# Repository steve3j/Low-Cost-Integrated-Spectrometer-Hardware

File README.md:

# Low-Cost-Integrated-Spectrometer-Hardware
Hardware for LCI Spectrometer - ECE 445 Senior Design project

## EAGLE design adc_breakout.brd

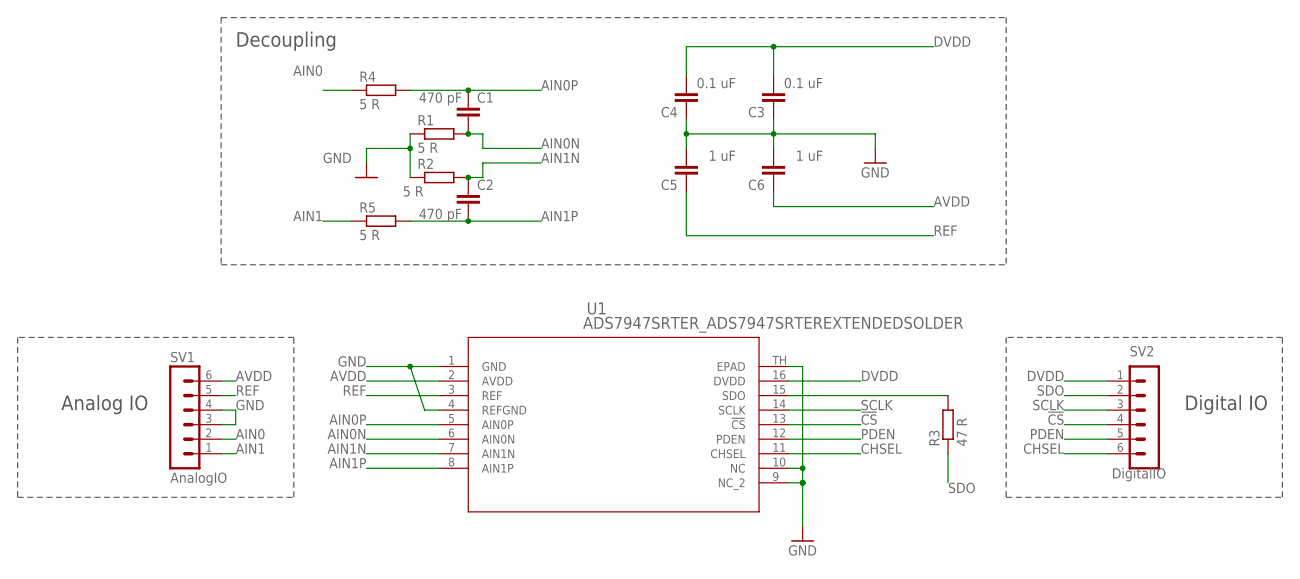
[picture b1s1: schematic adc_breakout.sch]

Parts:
C1, C2: 470 pF; C0603
C3, C4: 0.1 uF; C0603
C5, C6: 1 uF; C0603
R1, R2, R4, R5: 5 R; R0603
R3: 47 R; R0603
SV1: AnalogIO; MA06-1
SV2: DigitalIO; MA06-1
U1: ADS7947SRTER_ADS7947SRTEREXTENDEDSOLDER; QFN16-EXTENDEDPADS

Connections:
!CS: SV2.4, U1.13 (!CS)
AIN0: R4.1, SV1.2
AIN0N: C1.2, R1.2, U1.6 (AIN0N)
AIN0P: C1.1, R4.2, U1.5 (AIN0P)
AIN1: R5.1, SV1.1
AIN1N: C2.1, R2.2, U1.7 (AIN1N)
AIN1P: C2.2, R5.2, U1.8 (AIN1P)
AVDD: C6.1, SV1.6, U1.2 (AVDD)
CHSEL: SV2.6, U1.11 (CHSEL)
DVDD: C3.2, C4.2, SV2.1, U1.16 (DVDD)
GND: C3.1, C4.1, C5.2, C6.2, R1.1, R2.1, SV1.3, SV1.4, U1.1 (GND), U1.4 (REFGND), U1.9 (NC_2), U1.10 (NC), U1.TH (EPAD)
unnamed: R3.2, U1.15 (SDO)
PDEN: SV2.5, U1.12 (PDEN)
REF: C5.1, SV1.5, U1.3 (REF)
SCLK: SV2.3, U1.14 (SCLK)
SDO: R3.1, SV2.2

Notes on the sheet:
Decoupling
Analog IO
Digital IO

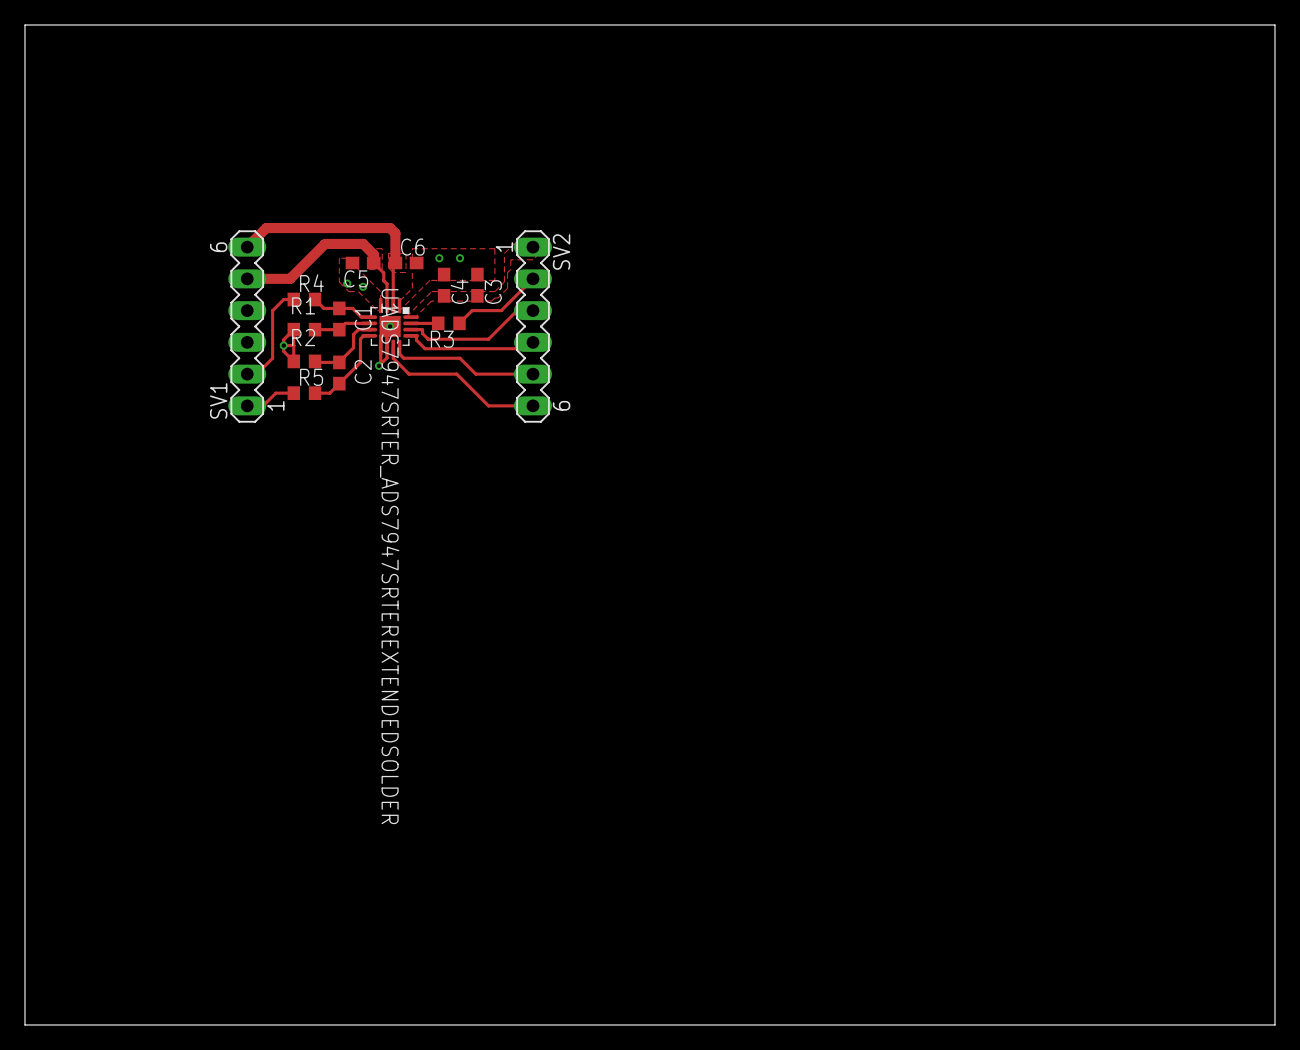
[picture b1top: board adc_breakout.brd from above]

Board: 2 copper layers, 100.0 x 80.0 mm, 14 parts (0 on the bottom side), 16 nets.

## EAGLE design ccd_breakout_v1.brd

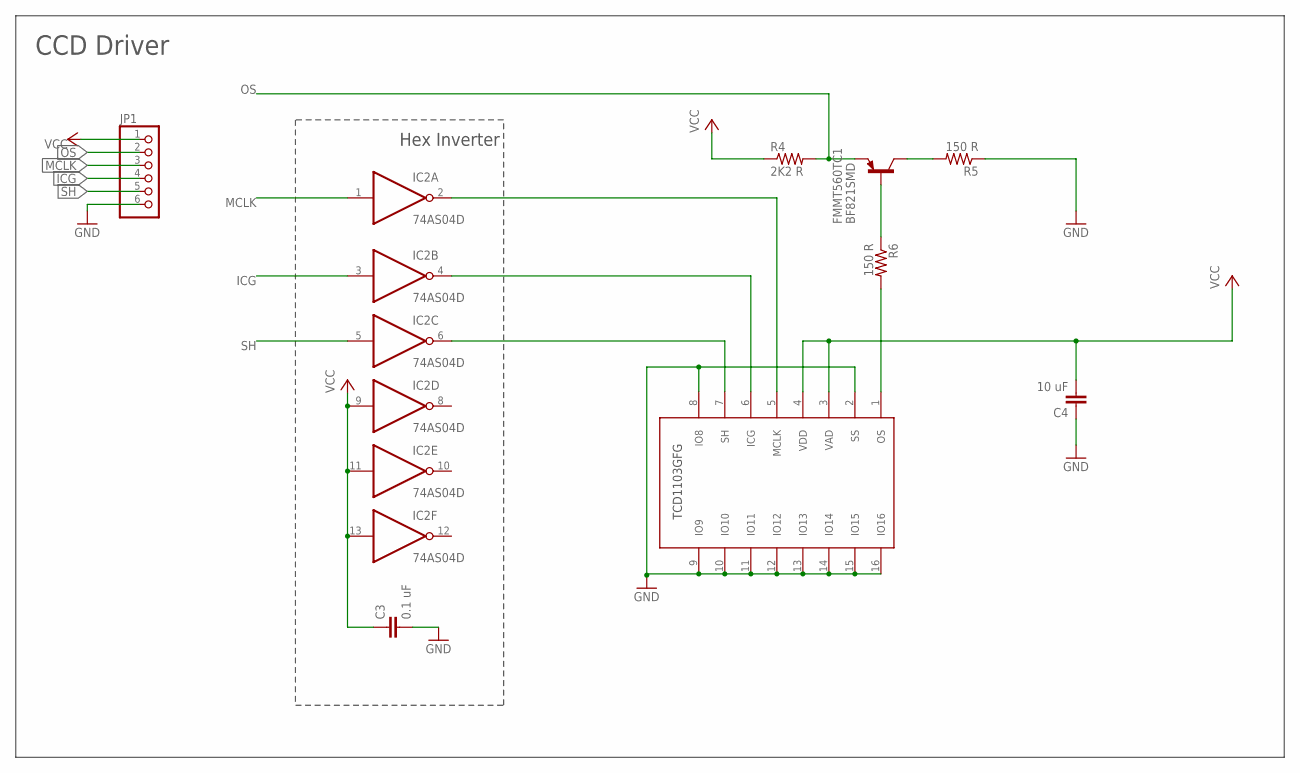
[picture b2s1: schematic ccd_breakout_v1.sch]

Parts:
C3: 0.1 uF; C1210
C4: 10 uF; C1210
FMMT560TC1: BF821SMD; SOT23-BEC
IC2: 74AS04D; SO14
JP1: PINHD-1X6; 1X06
R4: 2K2 R; R1206
R5, R6: 150 R; R1206
U$1: TCD1103_TCD1103; TCD1103_WQFN16X-240B

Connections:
GND: C3.2, C4.1, IC2.7 (GND), JP1.6, R5.1, U$1.2 (SS), U$1.8 (IO8), U$1.9 (IO9), U$1.10 (IO10), U$1.11 (IO11), U$1.12 (IO12), U$1.13 (IO13), U$1.14 (IO14), U$1.15 (IO15), U$1.16 (IO16)
ICG: IC2.3 (I), JP1.4
MCLK: IC2.1 (I), JP1.3
unnamed: FMMT560TC1.C, R5.2
unnamed: FMMT560TC1.B, R6.1
unnamed: R6.2, U$1.1 (OS)
unnamed: IC2.2 (O), U$1.5 (MCLK)
unnamed: IC2.4 (O), U$1.6 (ICG)
unnamed: IC2.6 (O), U$1.7 (SH)
OS: FMMT560TC1.E, JP1.2, R4.2
SH: IC2.5 (I), JP1.5
VCC: C3.1, C4.2, IC2.9 (I), IC2.11 (I), IC2.13 (I), IC2.14 (VCC), JP1.1, R4.1, U$1.3 (VAD), U$1.4 (VDD)

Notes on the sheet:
Hex Inverter
CCD Driver

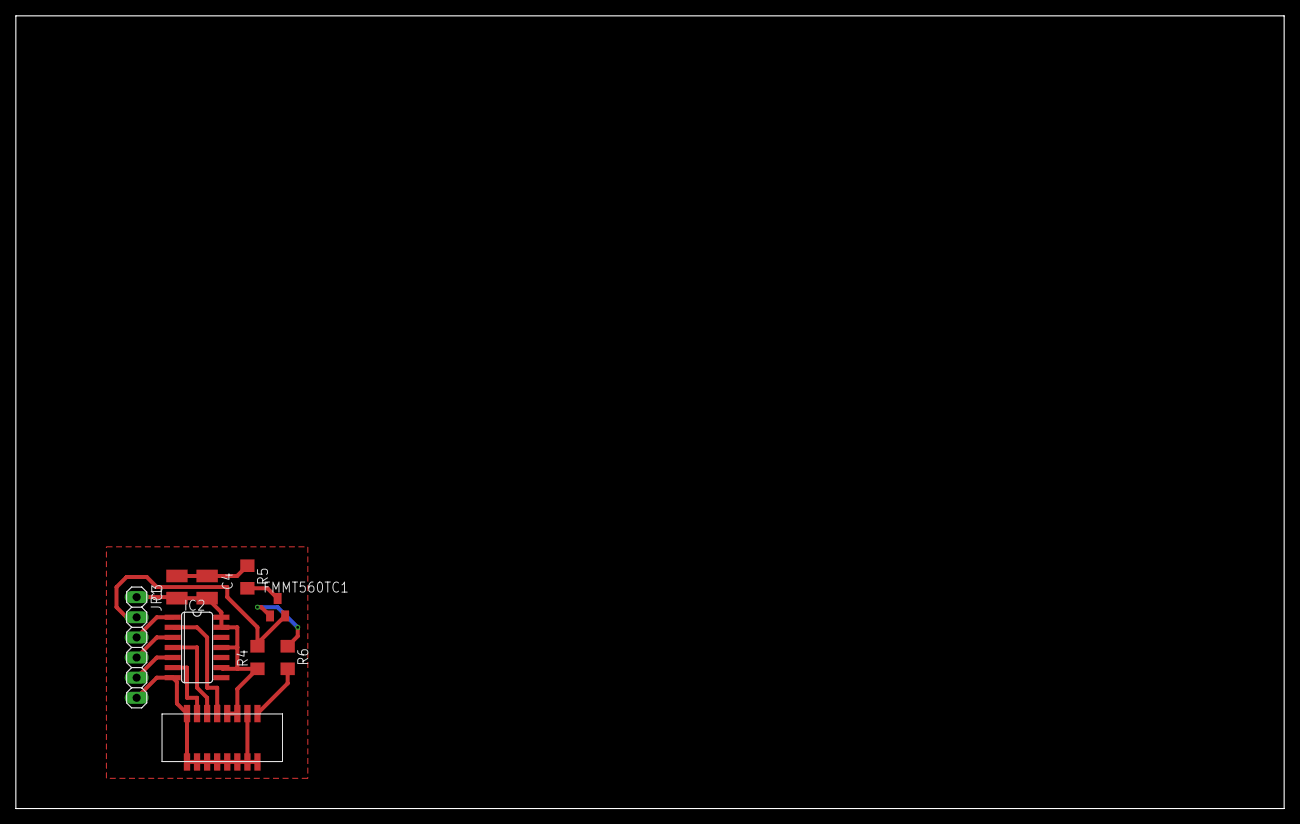
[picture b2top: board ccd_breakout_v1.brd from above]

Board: 2 copper layers, 160.0 x 100.0 mm, 9 parts (0 on the bottom side), 12 nets.

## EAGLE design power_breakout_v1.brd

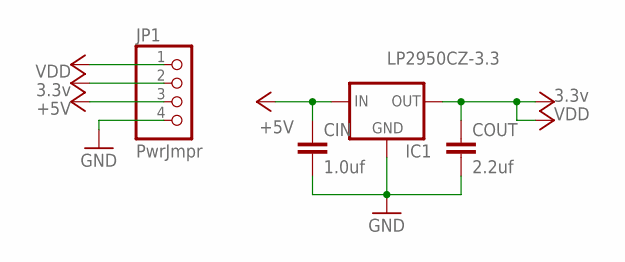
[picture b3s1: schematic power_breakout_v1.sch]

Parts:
CIN: 1.0uf; C025-025X050
COUT: 2.2uf; C025-025X050
IC1: LP2950CZ-3.3; TO92
JP1: PwrJmpr; 1X04

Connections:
+5V: CIN.1, IC1.3 (IN), JP1.3
GND: CIN.2, COUT.2, IC1.2 (GND), JP1.4
VCC: COUT.1, IC1.1 (OUT), JP1.1, JP1.2

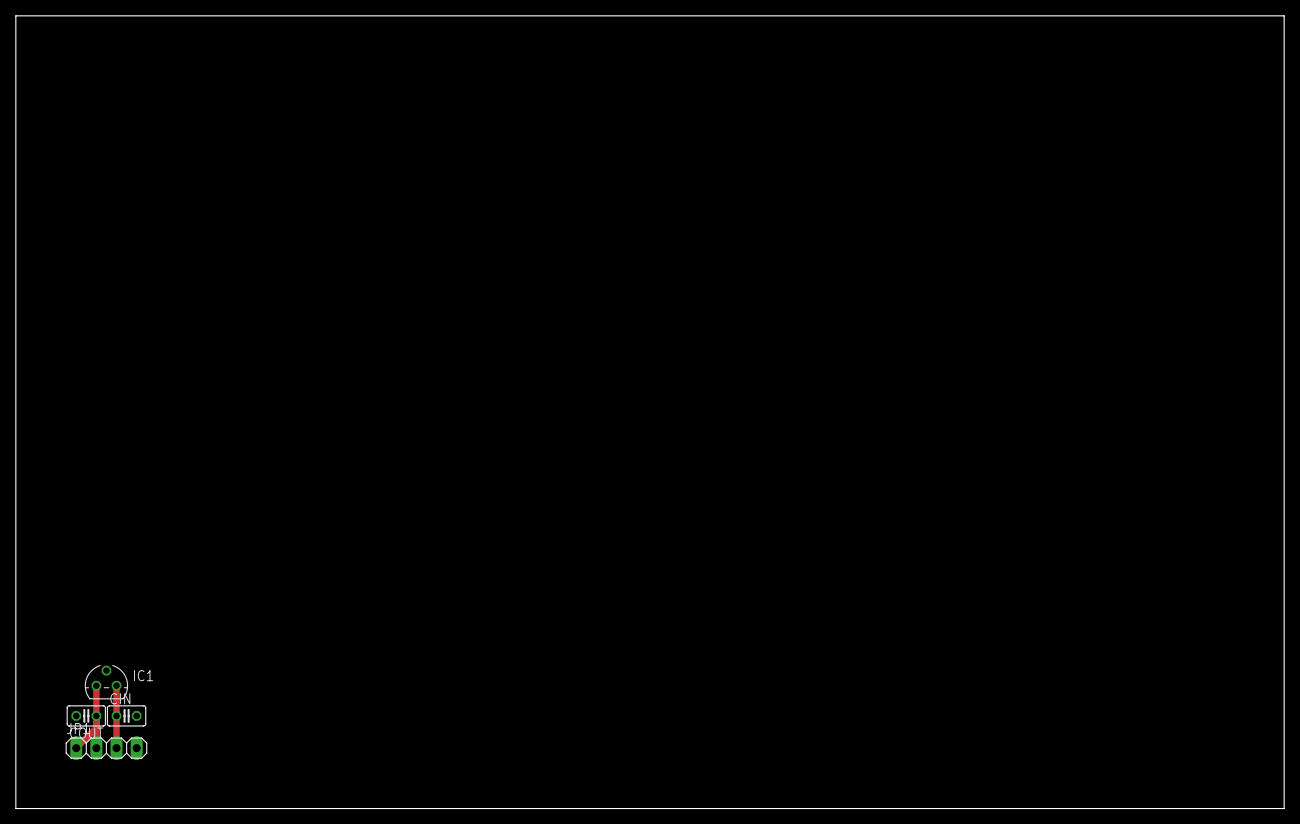
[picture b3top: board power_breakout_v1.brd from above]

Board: 2 copper layers, 160.0 x 100.0 mm, 4 parts (0 on the bottom side), 3 nets.

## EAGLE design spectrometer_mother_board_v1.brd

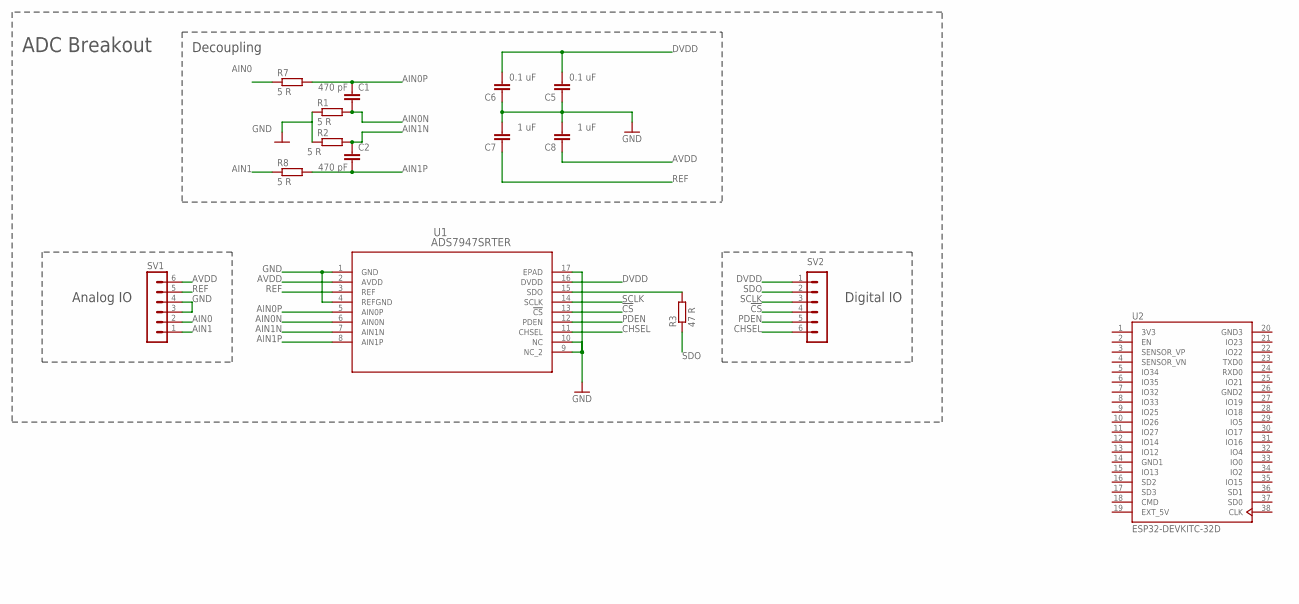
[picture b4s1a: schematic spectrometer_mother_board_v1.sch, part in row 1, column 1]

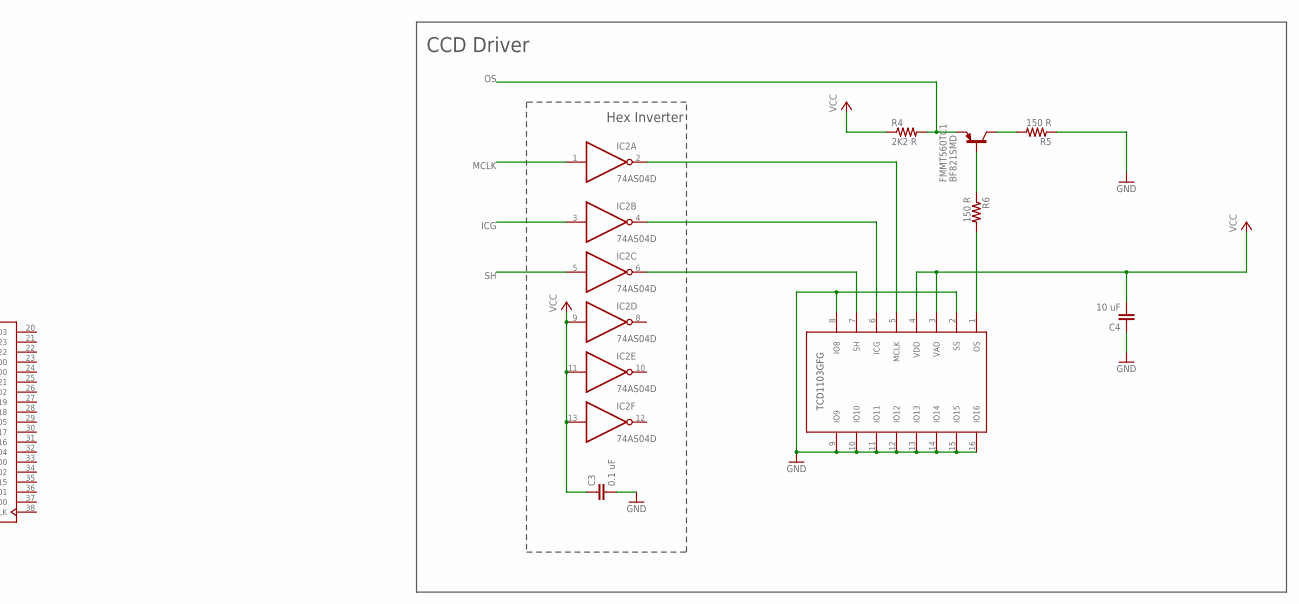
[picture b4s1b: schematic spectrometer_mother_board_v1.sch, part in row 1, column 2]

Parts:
C1, C2: 470 pF; C0603
C3: 0.1 uF; C1210
C4: 10 uF; C1210
C5, C6: 0.1 uF; C0603
C7, C8: 1 uF; C0603
FMMT560TC1: BF821SMD; SOT23-BEC
IC2: 74AS04D; SO14
R1, R2, R7, R8: 5 R; R0603
R3: 47 R; R0603
R4: 2K2 R; R1206
R5, R6: 150 R; R1206
SV1, SV2: MA06-1
U1: ADS7947SRTER; RTE16_1P7X1P7
U2: ESP32-DEVKITC-32D; MODULE_ESP32-DEVKITC-32D
U$2: TCD1103; GLCC16

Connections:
3V3: U2.1 (3V3)
!CS: SV2.4, U1.13 (!CS)
AIN0: R7.1, SV1.2
AIN0N: C1.2, R1.2, U1.6 (AIN0N)
AIN0P: C1.1, R7.2, U1.5 (AIN0P)
AIN1: R8.1, SV1.1
AIN1N: C2.1, R2.2, U1.7 (AIN1N)
AIN1P: C2.2, R8.2, U1.8 (AIN1P)
AVDD: C8.1, SV1.6, U1.2 (AVDD)
CHSEL: SV2.6, U1.11 (CHSEL)
DVDD: C5.2, C6.2, SV2.1, U1.16 (DVDD)
EXT_5V: U2.19 (EXT_5V)
GND: C3.2, C4.1, C5.1, C6.1, C7.2, C8.2, IC2.7 (GND), R1.1, R2.1, R5.1, SV1.3, SV1.4, U1.1 (GND), U1.4 (REFGND), U1.9 (NC_2), U1.10 (NC), U1.17 (EPAD), U$2.2 (SS), U$2.8 (IO8), U$2.9 (IO9), U$2.10 (IO10), U$2.11 (IO11), U$2.12 (IO12), U$2.13 (IO13), U$2.14 (IO14), U$2.15 (IO15), U$2.16 (IO16)
GND1: U2.14 (GND1)
GND2: U2.26 (GND2)
GND3: U2.20 (GND3)
ICG: IC2.3 (I)
MCLK: IC2.1 (I)
unnamed: FMMT560TC1.C, R5.2
unnamed: FMMT560TC1.B, R6.1
unnamed: R6.2, U$2.1 (OS)
unnamed: IC2.2 (O), U$2.5 (MCLK)
unnamed: IC2.4 (O), U$2.6 (ICG)
unnamed: IC2.6 (O), U$2.7 (SH)
OS: FMMT560TC1.E, R4.2
PDEN: SV2.5, U1.12 (PDEN)
REF: C7.1, SV1.5, U1.3 (REF)
SCLK: SV2.3, U1.14 (SCLK)
SDO: R3.1, R3.2, SV2.2, U1.15 (SDO)
SH: IC2.5 (I)
VCC: C3.1, C4.2, IC2.9 (I), IC2.11 (I), IC2.13 (I), IC2.14 (VCC), R4.1, U$2.3 (VAD), U$2.4 (VDD)

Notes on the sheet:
Hex Inverter
CCD Driver
Decoupling
Analog IO
Digital IO
ADC Breakout

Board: 2 copper layers, 23 parts (0 on the bottom side), 23 nets, no tracks yet.

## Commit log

2020-03-09 initial
2020-03-10 ccdDone
2020-03-11 rm all files to reset
2020-03-12 pcbWayCheckPassed
2020-03-12 checkOK
